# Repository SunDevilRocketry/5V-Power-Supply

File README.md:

<h1>5V Power Supply</h1>

<p>Current PCB Revision: 1.0</p>

<p>PCB Part Number: A0003</p>

<p>The 5V power supply is a DC-DC switching power supply prototype board for
testing the A0002 power supply. The board uses a buck converter circuit to regulate high voltages to 5V efficiently. </p>

<p><b>Working Directory Structure:</b></p>
  
<p>
  doc: documentation
  
  src: source design files, e.g. schematic and PCB layout files
  
  lib: libraries for schematic symbols and footprints
 
  production: files needed for pcb fabrication, e.g. gerbers, profile, drill 
              files
 
  sim: simulation files
 
  cad: 3d models

  img: images of circuit/footprints for github display
</p>

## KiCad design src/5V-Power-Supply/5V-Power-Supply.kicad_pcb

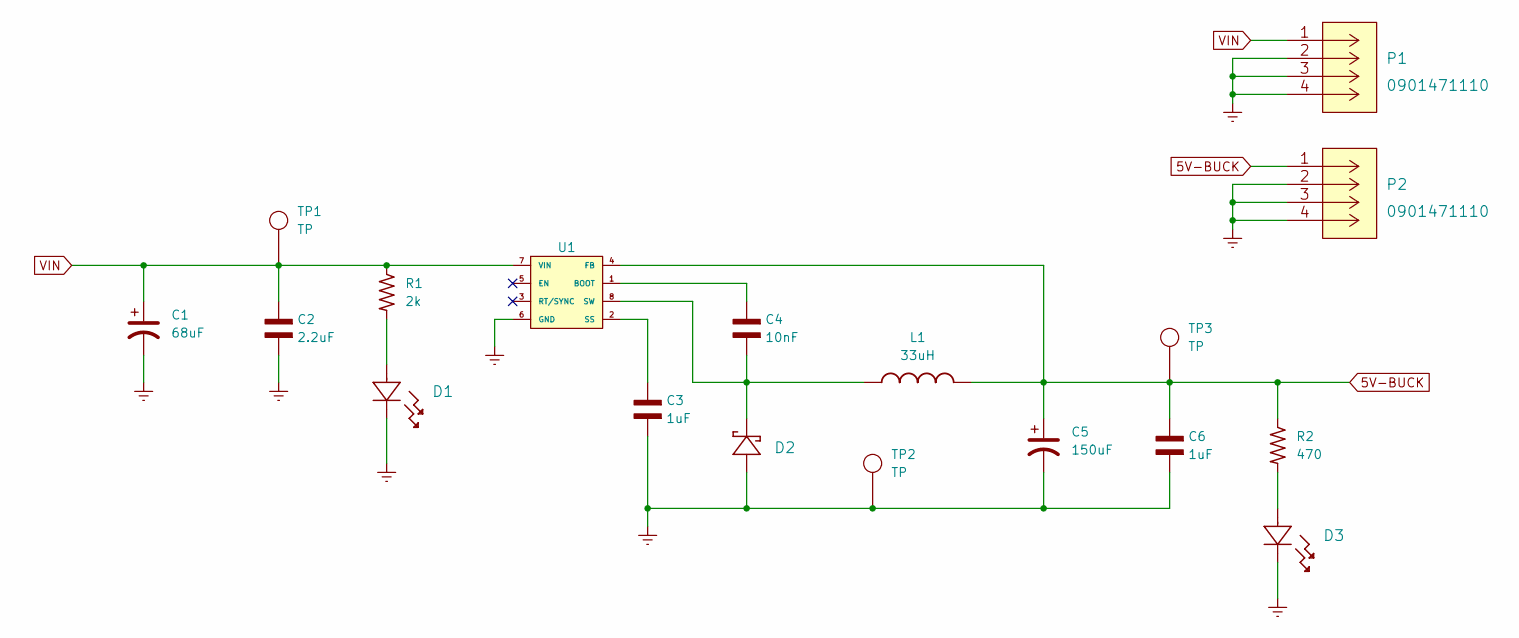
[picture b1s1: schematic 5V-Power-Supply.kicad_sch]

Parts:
C1: 68uF; EEEFPV680XAP
C2: 2.2uF; CAP_0603
C3, C6: 1uF; CAP_0603
C4: 10nF; CAP_0603
C5: 150uF; CAP_EEEFP1E151AL
D1, D3: SML-LX1206GC-TR
D2: RB160VAM-60TR
L1: 33uH; CBC3225T220KR
P1, P2: 0901471110; PinHeader_1x04_P1.00mm_Horizontal
R1: 2k; RES_0603
R2: 470; RES_0603
TP1, TP2, TP3: TP
U1: LM22672MRE-5.0_NOPB

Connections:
5V-BUCK: C5.1, C6.1, L1.2, P2.1, R2.1, TP3.1, U1.4 (FB)
Earth: C1.2, C2.2, C3.2, C5.2, C6.2, D1.1, D2.2, D3.1, P1.2, P1.3, P1.4, P2.2, P2.3, P2.4, TP2.1, U1.6 (GND)
unnamed: C3.1, U1.2 (SS)
unnamed: C4.1, U1.1 (BOOT)
unnamed: C4.2, D2.1, L1.1, U1.8 (SW)
unnamed: D1.2, R1.2
unnamed: D3.2, R2.2
VIN: C1.1, C2.1, P1.1, R1.1, TP1.1, U1.7 (VIN)

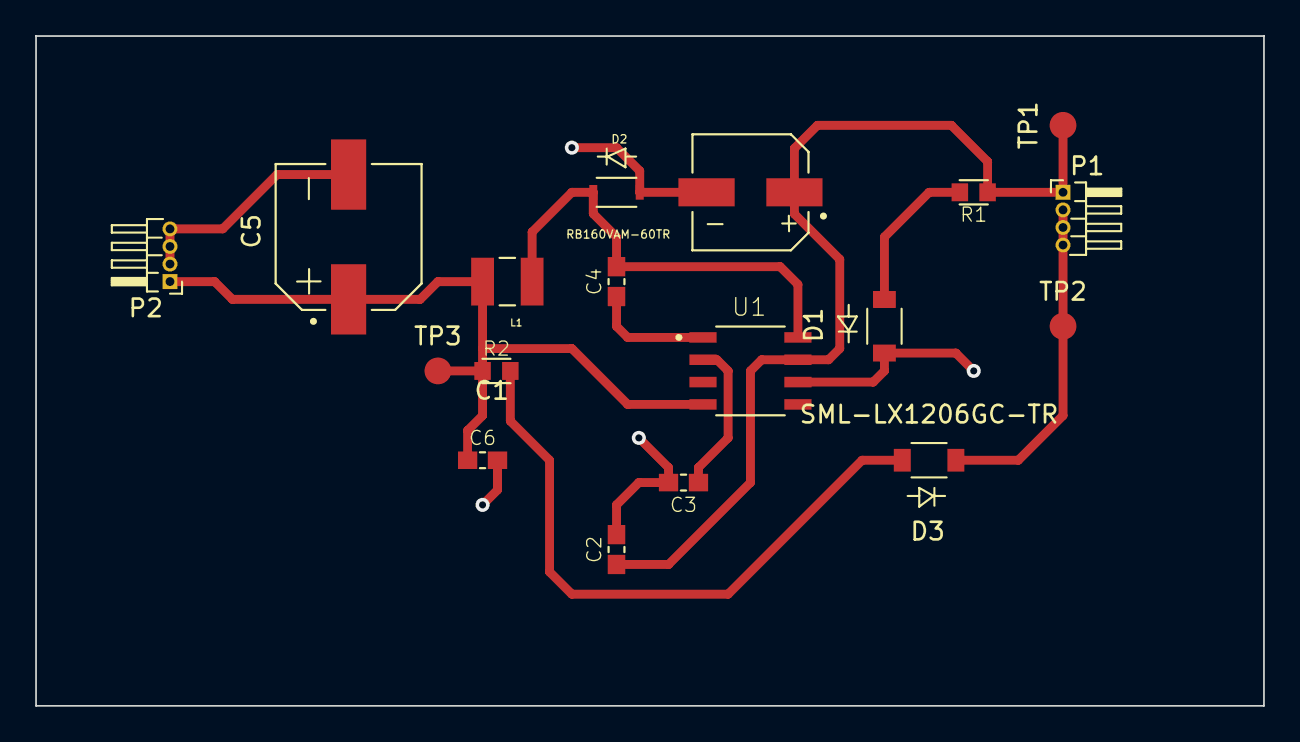
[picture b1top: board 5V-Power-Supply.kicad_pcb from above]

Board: 2 copper layers, 69.9 x 38.1 mm, 18 parts (0 on the bottom side), 8 nets.

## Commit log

2022-12-24 copied over files from old repository

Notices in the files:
parts and their libraries:
Copyright 2021 Accelerated Designs. All rights reserved.
